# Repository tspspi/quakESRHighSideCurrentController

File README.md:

# Simple 500 mA high voltage biasable current source

This project contains a simple OpAmp and MosFET based current supply
that can be controlled using a serial port. The whole project is built
around an ```IRF540N``` MosFET that's driven by an ```LM358``` OpAmp in a way
to keep the voltage drop over a sense resistor constant - thus it provides
a controllable current source (note that there is no temperature compensation
but that was not necessary for this application).

The reference voltage is provided by an ```MCP4822``` SPI digital to analog
converter that's controlled by an ```ATMega328P```. The serial port that's used
to control the current source is isolated using two ```PC816``` optocouplers - this
is necessary since the whole board will be biased to ```-2 kV``` with respect to the
controlling system. The load is powered by an 12V isolation transformer, the controller
uses the same power supply and derives it's 5V supply for DAC and microcontroller using
a simple ```LM317``` linear voltage regulator.

## The schematic

The schematic can be found in KiCAD format in the ```/kicad/currentcontroller``` directory

## A PCB design

This repository includes also a simple PCB design

## Microcontroller firmware

The firmware for the microcontroller can be found in ```mcusrc``` and is built
using ```avr-gcc```. The firmware can be flashed by using the ```Makefile```:

```
make flash
```

The ACSL annotations are work in progress.

## Test script

To test the communication using a [simple serial TTL to USB converter](https://amzn.to/3C0tQMZ)
a simple Python library is available (currently no PyPi package) at ```mcusrc/sertest```

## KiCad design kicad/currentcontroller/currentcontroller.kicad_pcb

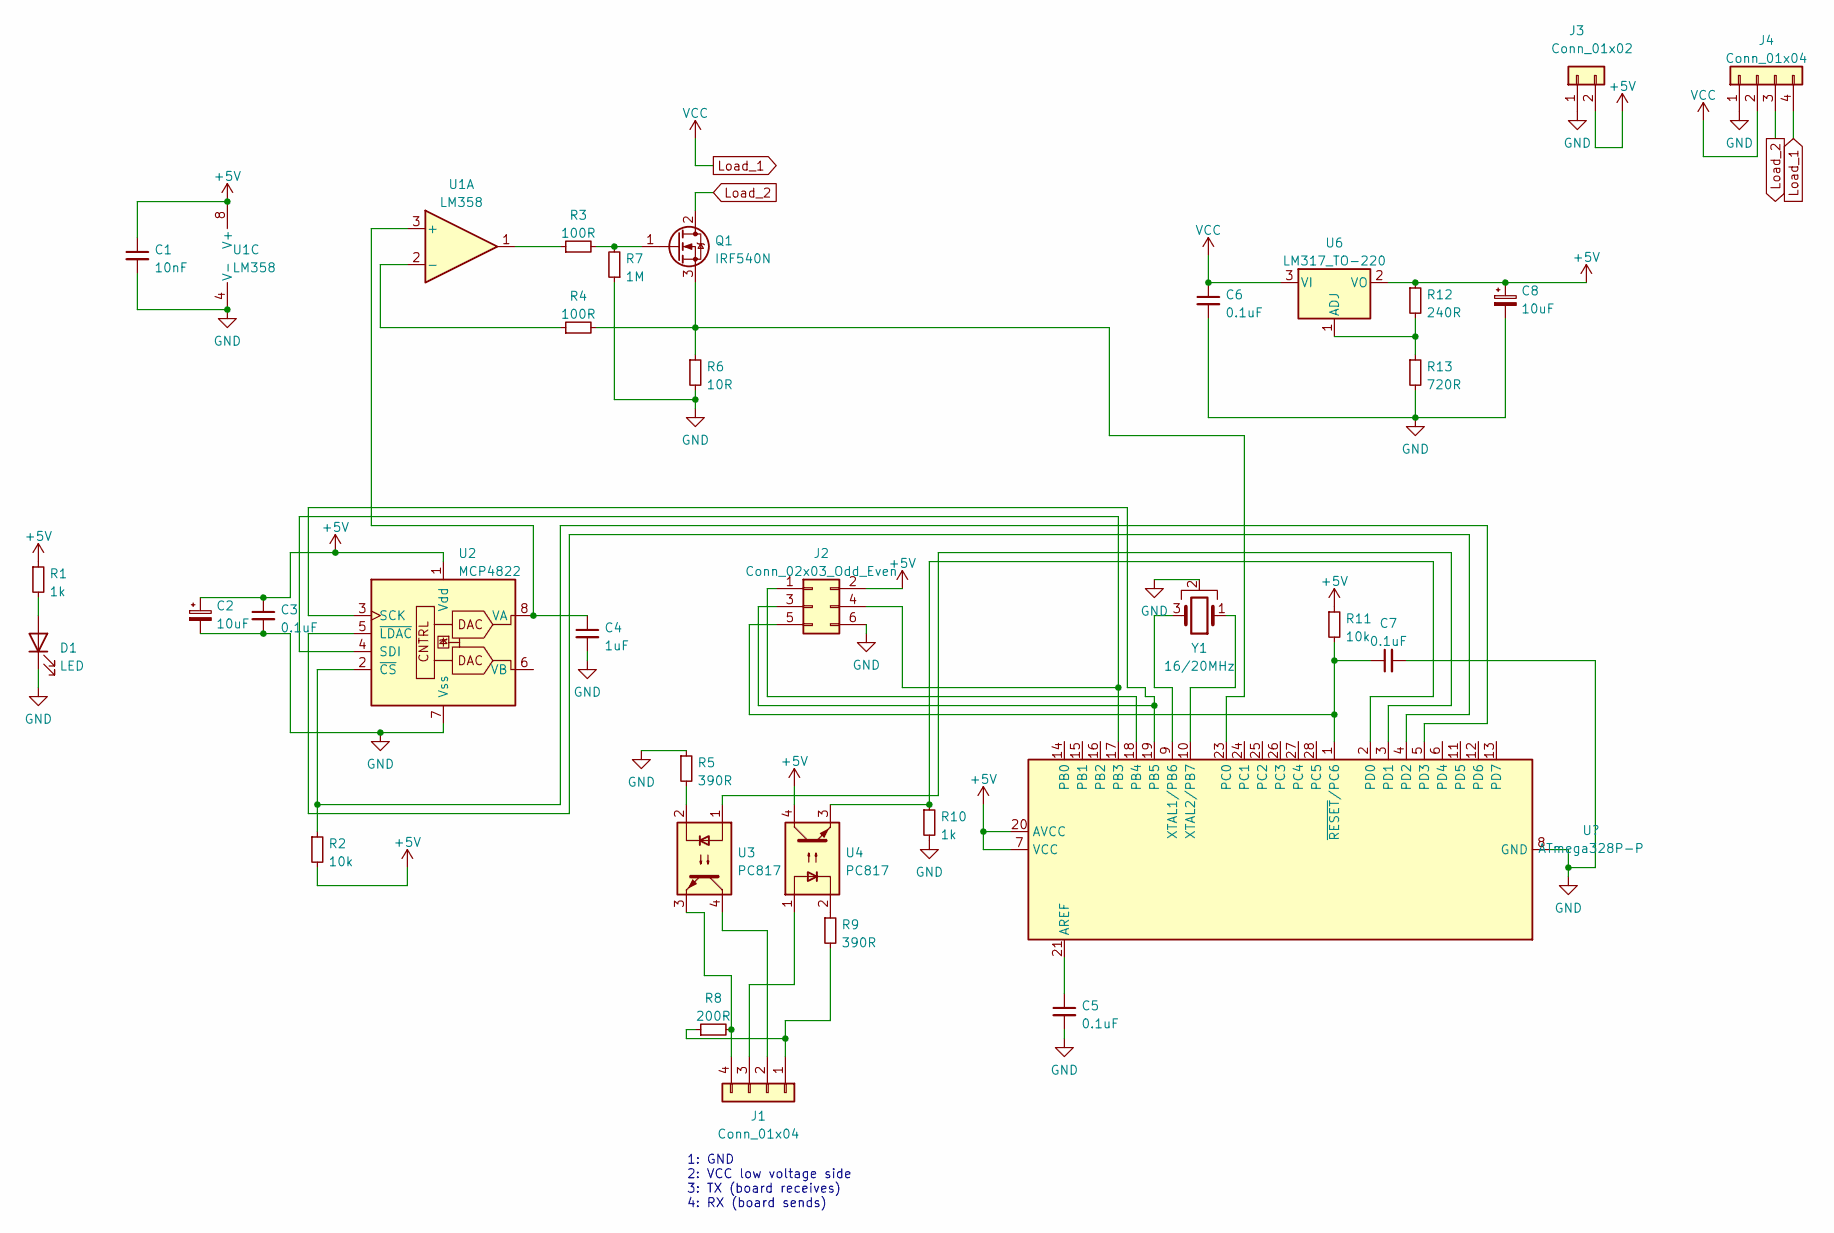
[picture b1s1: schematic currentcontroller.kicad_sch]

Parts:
C1: 10nF; C_Rect_L7.0mm_W2.0mm_P5.00mm
C2, C8: 10uF; CP_Radial_D5.0mm_P2.50mm
C3, C5, C6, C7: 0.1uF; C_Rect_L7.0mm_W2.0mm_P5.00mm
C4: 1uF; C_Rect_L7.0mm_W2.0mm_P5.00mm
D1: LED; LED_D5.0mm
J1, J4: Conn_01x04; PinHeader_1x04_P2.54mm_Horizontal
J2: Conn_02x03_Odd_Even; PinHeader_2x03_P2.54mm_Vertical
J3: Conn_01x02; PinHeader_1x02_P2.54mm_Horizontal
Q1: IRF540N; TO-220-3_Vertical
R1, R10: 1k; R_Axial_DIN0309_L9.0mm_D3.2mm_P12.70mm_Horizontal
R2, R11: 10k; R_Axial_DIN0309_L9.0mm_D3.2mm_P12.70mm_Horizontal
R3, R4: 100R; R_Axial_DIN0309_L9.0mm_D3.2mm_P12.70mm_Horizontal
R5, R9: 390R; R_Axial_DIN0309_L9.0mm_D3.2mm_P12.70mm_Horizontal
R6: 10R; R_Axial_DIN0309_L9.0mm_D3.2mm_P12.70mm_Horizontal
R7: 1M; R_Axial_DIN0309_L9.0mm_D3.2mm_P12.70mm_Horizontal
R8: 200R; R_Axial_DIN0309_L9.0mm_D3.2mm_P12.70mm_Horizontal
R12: 240R; R_Axial_DIN0309_L9.0mm_D3.2mm_P12.70mm_Horizontal
R13: 720R; R_Axial_DIN0309_L9.0mm_D3.2mm_P12.70mm_Horizontal
U1: LM358; DIP-8_W7.62mm
U2: MCP4822; MSOP-8_3x3mm_P0.65mm
U3, U4: PC817; DIP-4_W7.62mm
U6: LM317_TO-220; TO-220-3_Vertical
Y1: 16/20MHz; PinHeader_1x03_P2.54mm_Vertical

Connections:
+5V: C1.1, C2.1, C3.1, C8.1, J2.2, J3.2, R1.1, R2.2, R11.1, R12.1, U1.8 (V+), U2.1 (Vdd), U4.4, U6.2 (VO); also elsewhere on the board
GND: C1.2, C2.2, C3.2, C4.2, C5.2, C6.2, C7.2, C8.2, D1.1 (K), J2.6, J3.1, J4.1, R5.1, R6.2, R7.1, R10.2, R13.2, U1.4 (V-), U2.7 (Vss), Y1.2; also elsewhere on the board
Load_1: C6.1, J4.2, J4.4, U6.3 (VI)
Load_2: J4.3, Q1.2 (D)
unnamed: C4.1, U1.3 (+), U2.8 (VA)
unnamed 5: C5.1; also elsewhere on the board
unnamed 6: C7.1, J2.5, R11.2; also elsewhere on the board
unnamed: D1.2 (A), R1.2
unnamed: J1.1, R8.1, R9.2
unnamed: J1.2, U3.4
unnamed: J1.3, U4.1
unnamed: J1.4, R8.2, U3.3
unnamed 13: J2.3, U2.3 (SCK); also elsewhere on the board
unnamed 14: J2.4, U2.4 (SDI); also elsewhere on the board
unnamed: Q1.1 (G), R3.2, R7.2
unnamed 16: Q1.3 (S), R4.2, R6.1; also elsewhere on the board
unnamed 17: R2.1, U2.2 (~CS); also elsewhere on the board
unnamed: R3.1, U1.1
unnamed: R4.1, U1.2 (-)
unnamed: R5.2, U3.2
unnamed: R9.1, U4.2
unnamed 22: R10.1, U4.3; also elsewhere on the board
unnamed: R12.2, R13.1, U6.1 (ADJ)
unnamed 24: U2.5 (~LDAC); also elsewhere on the board
unnamed 25: U3.1; also elsewhere on the board
unnamed 26: Y1.1; also elsewhere on the board
unnamed 27: Y1.3; also elsewhere on the board

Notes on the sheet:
1: GND 2: VCC low voltage side 3: TX (board receives) 4: RX (board sends)

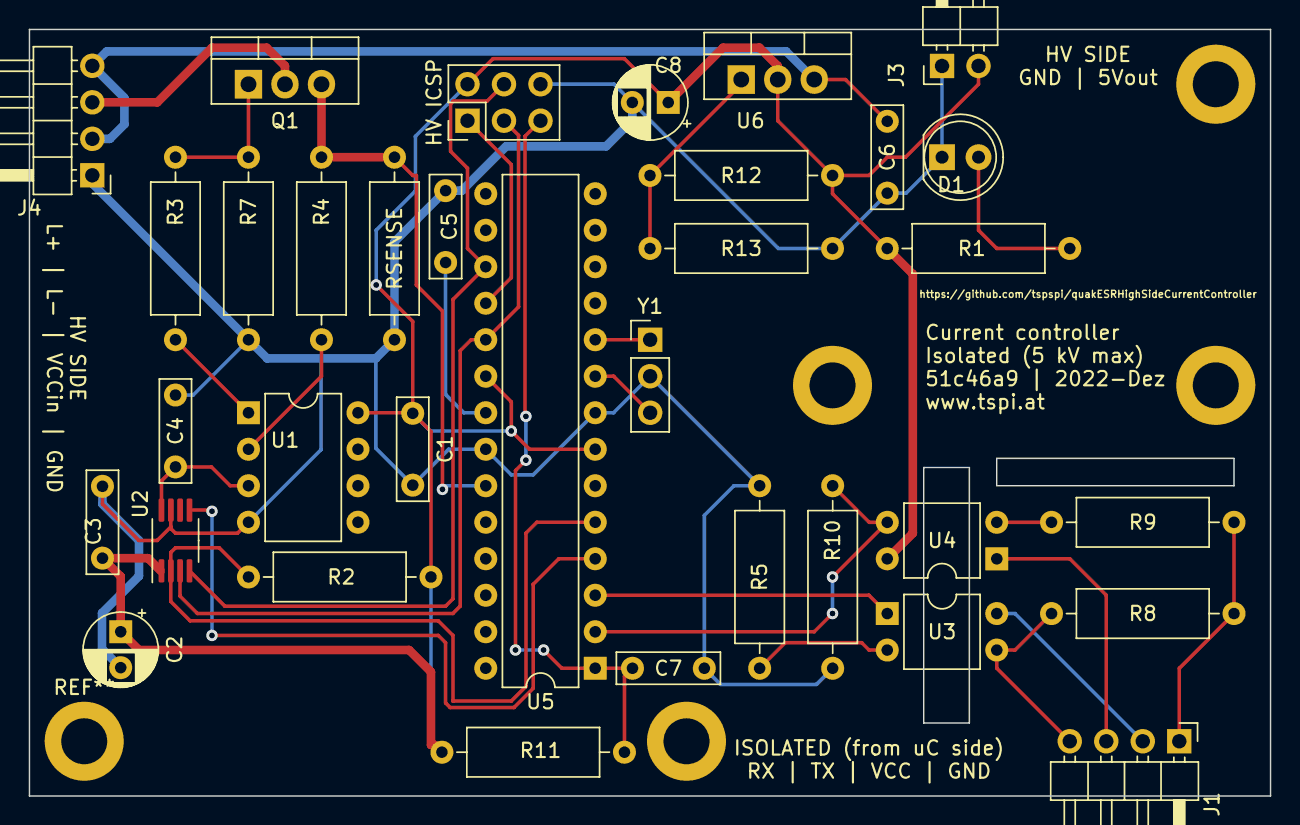
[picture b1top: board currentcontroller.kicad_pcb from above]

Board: 2 copper layers, 86.4 x 53.3 mm, 34 parts (0 on the bottom side), 28 nets.

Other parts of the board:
HV ICSP: Conn_02x03_Odd_Even; PinHeader_2x03_P2.54mm_Vertical
RSENSE: 10R; R_Axial_DIN0309_L9.0mm_D3.2mm_P12.70mm_Horizontal
U5: ATmega328P-P; DIP-28_W7.62mm

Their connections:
+5V: HV ICSP.2, U5.7 (VCC), U5.20 (AVCC); also elsewhere on the board
GND: HV ICSP.6, RSENSE.2, U5.8 (GND), U5.22 (GND); also elsewhere on the board
unnamed 5: U5.21 (AREF); also elsewhere on the board
unnamed 6: HV ICSP.5, U5.1 (~RESET/PC6); also elsewhere on the board
unnamed: HV ICSP.1, U5.18 (PB4)
unnamed 13: HV ICSP.3, U5.19 (PB5); also elsewhere on the board
unnamed 14: HV ICSP.4, U5.17 (PB3); also elsewhere on the board
unnamed 16: RSENSE.1, U5.23 (PC0); also elsewhere on the board
unnamed 17: U5.5 (PD3); also elsewhere on the board
unnamed 22: U5.2 (PD0); also elsewhere on the board
unnamed 24: U5.4 (PD2); also elsewhere on the board
unnamed 25: U5.3 (PD1); also elsewhere on the board
unnamed 26: U5.10 (XTAL2/PB7); also elsewhere on the board
unnamed 27: U5.9 (XTAL1/PB6); also elsewhere on the board

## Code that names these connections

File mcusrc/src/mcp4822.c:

#define __is_in_module__142e0c51_431e_11ed_9e74_b499badf00a1 1

#include <avr/io.h>
#include <avr/interrupt.h>
#include <math.h>

#include "main.h"
#include "mcp4822.h"

#ifdef __cplusplus
	extern "C" {
#endif

uint16_t mcp4822_CurrentValues[2] = { 0, 0 };

/*@
	requires \valid(&SPCR) && \valid(&SPSR) && \valid(&PORTD);

	assigns PORTD;
	assigns SPCR;
	assigns SPSR;

	ensures (PORTD & 0x08) == 0;
	ensures SPCR == 0x53;
	ensures SPSR == 0x01;
*/
static inline void mcp4822SPI_TransferBegin() {
	SPCR = 0x50 | 0x03;
	SPSR = 0x01;

	/* Chip select to low ... */
	PORTD = PORTD & (~(0x08));
}
/*@
	requires \valid(&SPCR) && \valid(&PORTD);

	assigns PORTD;
	assigns SPCR;

	ensures (PORTD & 0x08) == 0x08;
	ensures SPCR == 0x40;
*/
static inline void mcp4822SPI_TransferEnd() {
	SPCR = 0x40;
	PORTD = PORTD | 0x08;
}
/*@
	requires \valid(&SPDR) && \valid(&SPSR);

	assigns SPDR;

	ensures \result == SPDR;
*/
static inline uint8_t mcp4822SPI_Transfer(uint8_t byteOut) {
	SPDR = byteOut;
	asm volatile("nop");
	while((SPSR & 0x80) == 0) { }
	return SPDR;
}
/*@
	requires \valid(&PORTD);

	assigns PORTD;

	ensures (PORTD & 0x04) == 0x04;
*/
static inline void mcp4822SPI_LatchOutputs() {
	PORTD = PORTD & (~0x04);
	/* Two NOPs to reach 100 ns minimum time (at 16 MHz each is ~ 62 ns) */
	//@ assert (PORTD & 0x04) == 0;
	asm volatile("nop");
	asm volatile("nop");
	PORTD = PORTD | 0x04;
}

/*@
	requires \valid(&SREG) && \valid(&DDRD) && \valid(&PORTD) && \valid(&DDRB) && \valid(&SPCR) && \valid(&SPSR);

	assigns SREG;
	assigns DDRD, PORTD;
	assigns DDRB;
	assigns SPCR, SPSR;
	assigns PRR;

	ensures (DDRD & 0x0C) == 0x0C;
	ensures (PORTD & 0x0C) == 0x0C;
	ensures ((DDRB & 0x24) == 0x24) && ((DDRB & 0x10) == 0);
	ensures (SPCR = 0x40) && (SPSR == 0x01);
	ensures SREG == \old(SREG);
	ensures PRR & 0x04 == 0x00;
*/
void mcp4822Init() {
	uint8_t sregOld = SREG;
	#ifndef FRAMAC_SKIP
		cli();
	#endif

	/*
		Set I/O pins for SPI
			PD3 -> nCS
			PD2 -> nLDAC
			PB5 -> SCK
			PB3 -> SDI (MOSI)
			PB4 -> MISO

			PB2 is slave select, should be configured as output

		nCS -> output, high
		nLDAC -> output, high

	*/
	DDRD = DDRD | 0x0C;
	PORTD = PORTD | 0x0C;
	DDRB = (DDRB | 0x2C) & (~(0x10));
	PORTB = PORTB | 0x2C;

	/* Disable power saving mode ... */
	PRR = PRR & ~(0x04);

	/* SPI master mode, enable logic */
	SPCR = 0x40;
	SPSR = 0x01;

	SREG = sregOld;

	/* Set our output values to 0 */
	mcp4822SetOutput(0, 0, false, 0);
	mcp4822SetOutput(1, 0, false, 0);
}

/*@
	requires (channel == 1) || (channel == 0);
	requires (gain == 1) || (gain == 0);
	requires (enableOutput == true) || (enableOutput == false);
	requires (value > 0) && (value < 4096);

	assigns SPSR, SPCR, SPDR;
	assigns mcp4822_CurrentValues[0], mcp4822_CurrentValues[1];

	ensures mcp4822_CurrentValues[channel] == value;
*/
void mcp4822SetOutput(
	uint8_t channel,
	uint8_t gain,
	bool enableOutput,
	uint16_t value
) {
	uint16_t msg = 0x00;

	/* Prepare message */
	msg = (value & 0x0FFF);
	if(channel != 0) {
		msg = msg | 0x8000;
	}
	if(gain != 0) {
		msg = msg | 0x2000;
	}
	if(enableOutput == true) {
		msg = msg | 0x1000;
	}

	/* Transmit 2 bytes ...*/
	mcp4822SPI_TransferBegin();
	mcp4822SPI_Transfer((uint8_t)((msg & 0xFF00) >> 8));
	mcp4822SPI_Transfer((uint8_t)(msg & 0x00FF));
	mcp4822SPI_TransferEnd();
	mcp4822SPI_LatchOutputs();

	mcp4822_CurrentValues[channel] = value;
}

#ifdef __cplusplus
	} /* extern "C" { */
#endif

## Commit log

2022-09-27 Initial commit of controller software
2022-09-27 Adjusted to other DAC
2022-09-27 Continued development (support for MCP4822, minimal change in serial protocol)
2022-09-30 Other flash method, also setting lfuses
2022-09-30 Enabling interrupts & setting clock prescaler
2022-09-30 Fixed implementation (not ACSL!)
2022-09-30 Initialization (not corrected in ACSL!)
2022-10-03 Added calibration curve for measurement
2022-10-03 MCP4822 now allows readback of set value
2022-10-03 Added configuration for current limit (software side) and EEPROM offsets
2022-10-03 Serial communication
    * Implemented disableable protection
    * Implemented setting and getting commands for current
    * Implemented measurement
    * Implemented calibration commands
2022-10-03 Python test program for serial control (ex. using TTL<->USB adapter)
2022-10-03 Reflecting latest changes on PCB
2022-10-03 Added README and LICENSE
2022-10-10 Updating ACSL annotations
2022-10-10 Upading ACSL annotations
2022-11-02 Minor updates and finished PCB
2022-11-02 Added images of schematic and PCB
2022-11-02 Added gerber files used for PCBWay
2022-11-02 Updated gitignore
2022-12-12 Makefile update
    * Makefile now contains correct flags for 16 MHz crystal
    * Supports STK500 programmer via simple change to definitions
2022-12-12 Ability to simply define which channel to use for current measurement
2022-12-13 Changed ADC back to channel 0 (for new board)
2022-12-13 Missing 5V trace
2022-12-13 Added commit ID
    * Added commit ID
    * Added a second slot for isolated island
2025-11-04 Adding zenodo metadata
